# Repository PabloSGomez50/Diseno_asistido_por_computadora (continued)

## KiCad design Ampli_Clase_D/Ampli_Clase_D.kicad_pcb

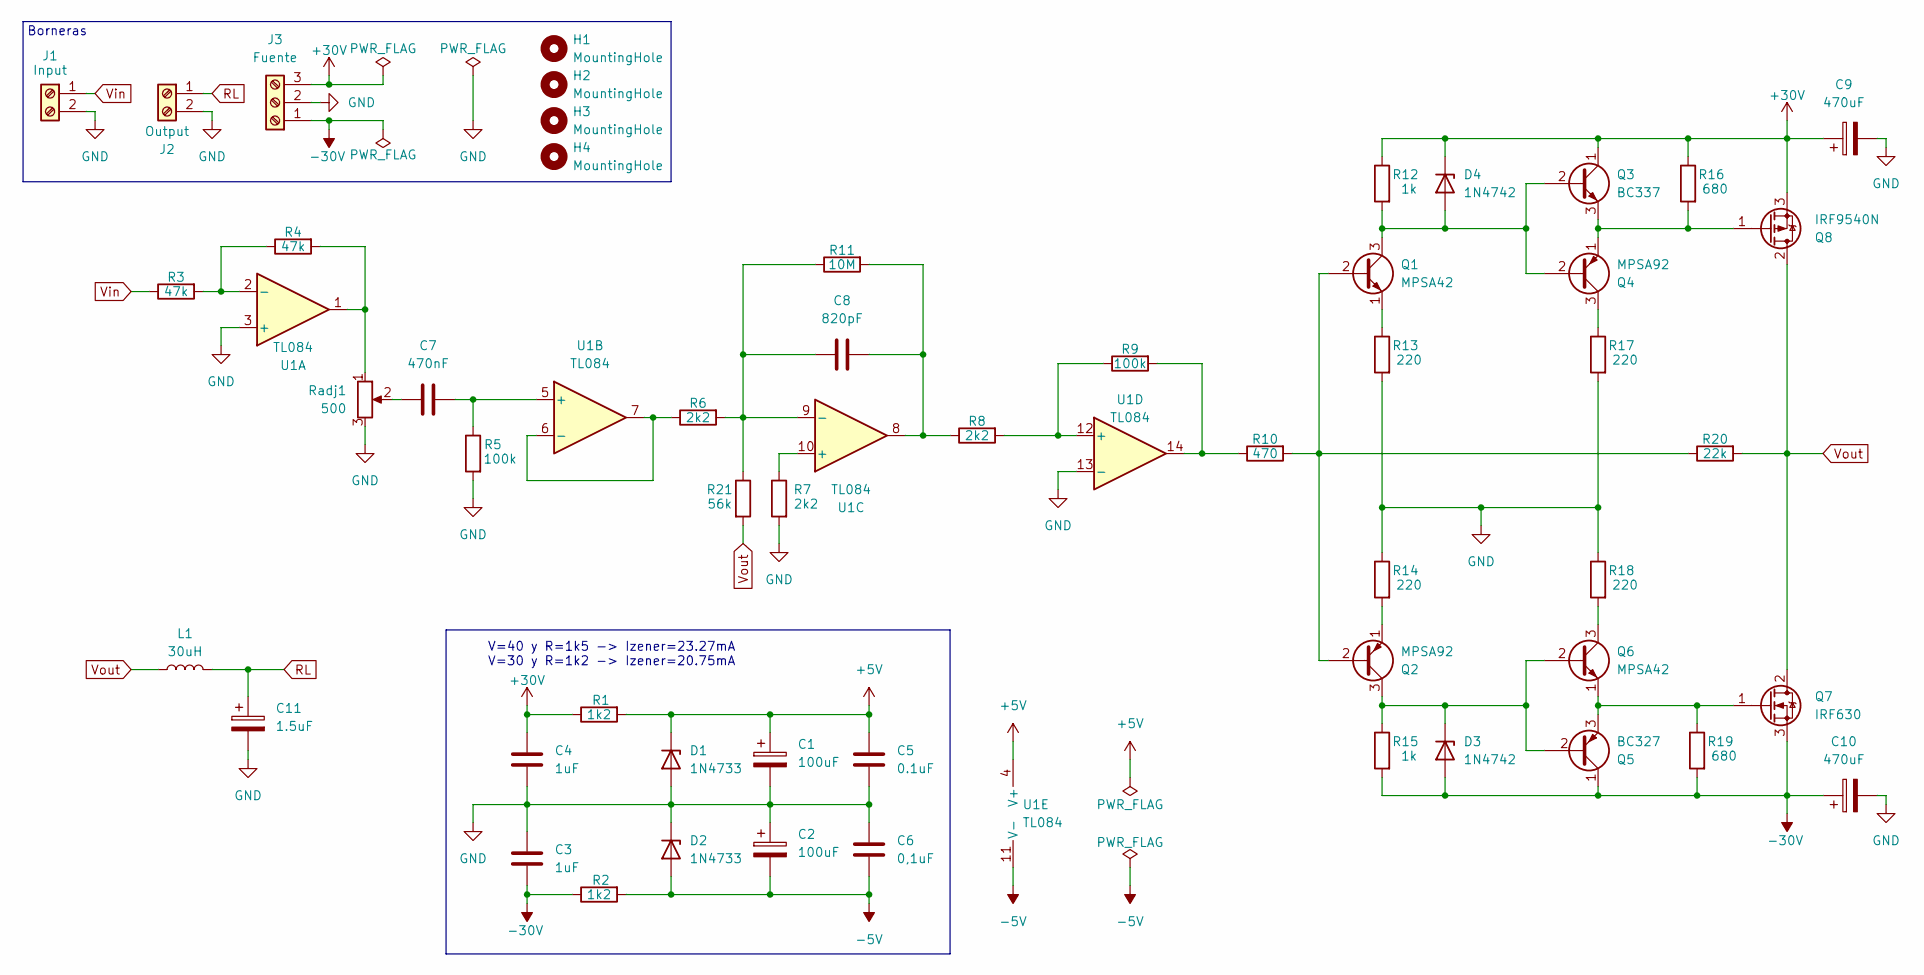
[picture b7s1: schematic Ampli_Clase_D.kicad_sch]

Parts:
C1, C2: 100uF; CP_Radial_D5.0mm_P2.50mm
C3, C4: 1uF; C_Disc_D3.0mm_W2.0mm_P2.50mm
C5: 0.1uF; C_Disc_D3.0mm_W2.0mm_P2.50mm
C6: 0,1uF; C_Disc_D3.0mm_W2.0mm_P2.50mm
C7: 470nF; C_Disc_D3.0mm_W2.0mm_P2.50mm
C8: 820pF; C_Disc_D3.0mm_W2.0mm_P2.50mm
C9, C10: 470uF; CP_Radial_D5.0mm_P2.50mm
C11: 1.5uF; CP_Radial_D5.0mm_P2.50mm
D1, D2: 1N4733; D_A-405_P10.16mm_Horizontal
D3, D4: 1N4742; D_A-405_P10.16mm_Horizontal
H1, H2, H3, H4: MountingHole; MountingHole_3.2mm_M3
J1: Input; TerminalBlock_Phoenix_MKDS-1,5-2-5.08_1x02_P5.08mm_Horizont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
J2: Output; TerminalBlock_Phoenix_MKDS-1,5-2-5.08_1x02_P5.08mm_Horizont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
J3: Fuente; TerminalBlock_Phoenix_MKDS-1,5-3-5.08_1x03_P5.08mm_Horizont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
L1: 30uH; Choke_Schaffner_RN204-04-9.0x14.0mm
Q1, Q6: MPSA42; TO-92_Inline
Q2, Q4: MPSA92; TO-92_Inline
Q3: BC337; TO-92_Inline
Q5: BC327; TO-92_Inline
Q7: IRF630; TO-220-3_Vertical
Q8: IRF9540N; TO-220-3_Vertical
R1, R2: 1k2; R_Axial_DIN0207_L6.3mm_D2.5mm_P10.16mm_Horizontal
R3, R4: 47k; R_Axial_DIN0207_L6.3mm_D2.5mm_P10.16mm_Horizontal
R5, R9: 100k; R_Axial_DIN0207_L6.3mm_D2.5mm_P10.16mm_Horizontal
R6, R7, R8: 2k2; R_Axial_DIN0207_L6.3mm_D2.5mm_P10.16mm_Horizontal
R10: 470; R_Axial_DIN0207_L6.3mm_D2.5mm_P10.16mm_Horizontal
R11: 10M; R_Axial_DIN0207_L6.3mm_D2.5mm_P10.16mm_Horizontal
R12, R15: 1k; R_Axial_DIN0207_L6.3mm_D2.5mm_P10.16mm_Horizontal
R13, R14, R17, R18: 220; R_Axial_DIN0207_L6.3mm_D2.5mm_P10.16mm_Horizontal
R16, R19: 680; R_Axial_DIN0207_L6.3mm_D2.5mm_P10.16mm_Horizontal
R20: 22k; R_Axial_DIN0207_L6.3mm_D2.5mm_P10.16mm_Horizontal
R21: 56k; R_Axial_DIN0207_L6.3mm_D2.5mm_P10.16mm_Horizontal
Radj1: 500; PinHeader_1x03_P2.54mm_Vertical
U1: TL084; DIP-14_W7.62mm

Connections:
+5V: C1.1, C5.1, D1.1 (K), R1.2, U1.4 (V+)
+30V: C4.1, C9.1, D4.1 (K), J3.3, Q3.1 (C), Q8.3 (S), R1.1, R12.1, R16.1
-5V: C2.2, C6.2, D2.2 (A), R2.2, U1.11 (V-)
-30V: C3.2, C10.1, D3.2 (A), J3.1, Q5.1 (C), Q7.3 (S), R2.1, R15.2, R19.2
GND: C1.2, C2.1, C3.1, C4.2, C5.2, C6.1, C9.2, C10.2, C11.2, D1.2 (A), D2.1 (K), J1.2, J2.2, J3.2, R5.2, R7.2, R13.2, R14.1, R17.2, R18.1, Radj1.3, U1.3 (+), U1.13 (-)
unnamed: C7.1, Radj1.2
unnamed: C8.2, R8.1, R11.2, U1.8
unnamed: D3.1 (K), Q2.3 (C), Q5.2 (B), Q6.2 (B), R15.1
unnamed: D4.2 (A), Q1.3 (C), Q3.2 (B), Q4.2 (B), R12.2
unnamed: Q1.2 (B), Q2.2 (B), R10.2, R20.1
unnamed: Q1.1 (E), R13.1
unnamed: Q2.1 (E), R14.2
unnamed: Q3.3 (E), Q4.1 (E), Q8.1 (G), R16.2
unnamed: Q4.3 (C), R17.1
unnamed: Q5.3 (E), Q6.1 (E), Q7.1 (G), R19.1
unnamed: Q6.3 (C), R18.2
unnamed: R4.2, Radj1.1, U1.1
unnamed: R9.2, R10.1, U1.14
unnamed: R3.2, R4.1, U1.2 (-)
unnamed: C7.2, R5.1, U1.5 (+)
unnamed: R6.1, U1.6 (-), U1.7
unnamed: R7.1, U1.10 (+)
unnamed: C8.1, R6.2, R11.1, R21.1, U1.9 (-)
unnamed: R8.2, R9.1, U1.12 (+)
RL: C11.1, J2.1, L1.2
Vin: J1.1, R3.1
Vout: L1.1, Q7.2 (D), Q8.2 (D), R20.2, R21.2

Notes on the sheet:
Borneras
V=40 y R=1k5 -> Izener=23.27mA V=30 y R=1k2 -> Izener=20.75mA

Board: 2 copper layers, 54 parts (0 on the bottom side), 27 nets, no tracks yet.

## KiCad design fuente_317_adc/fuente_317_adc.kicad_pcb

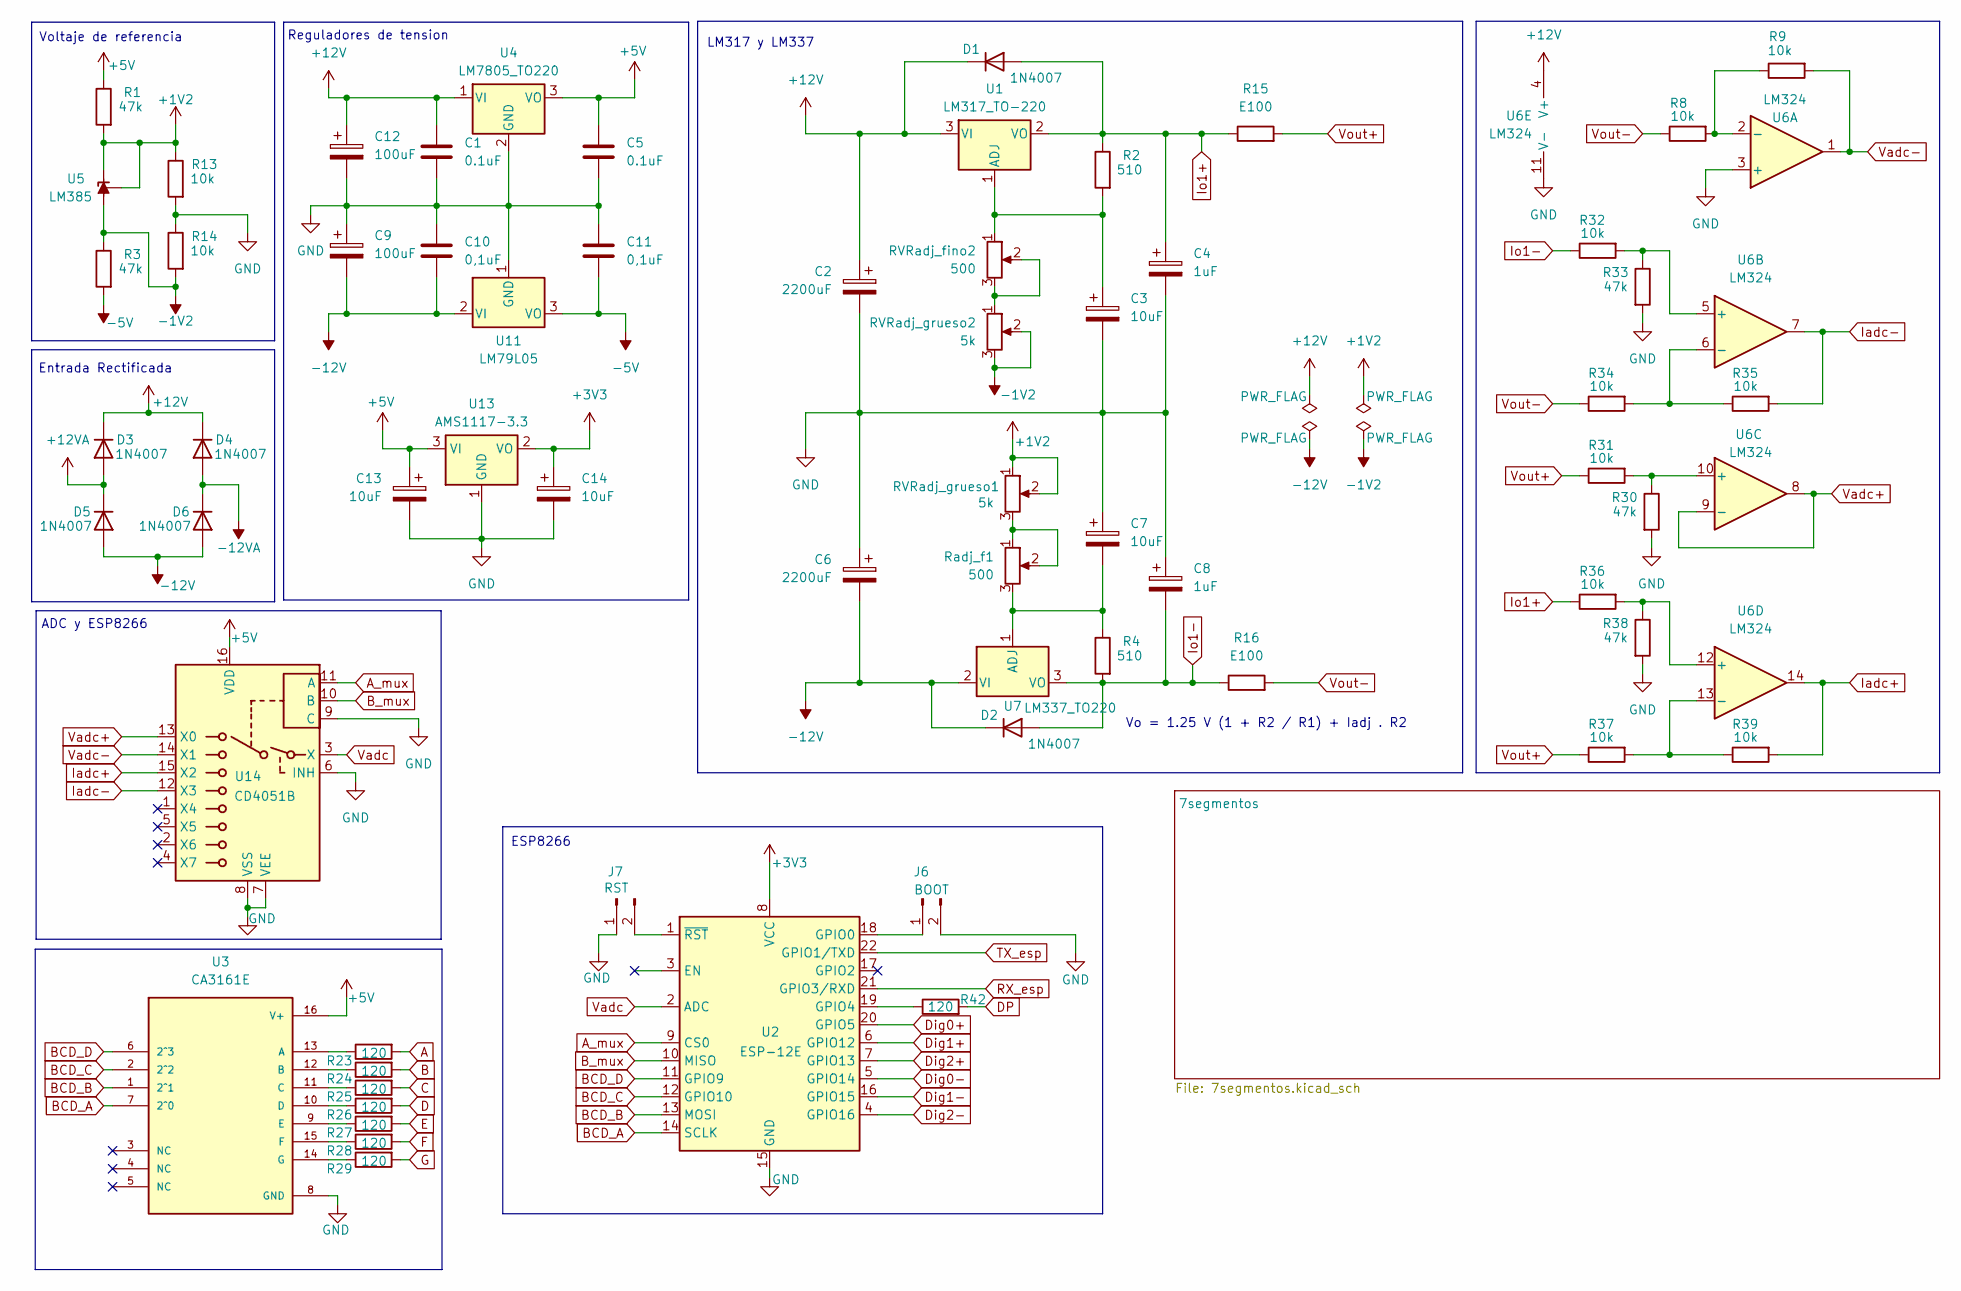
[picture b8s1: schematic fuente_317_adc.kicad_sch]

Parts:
C1, C5: 0.1uF; C_Disc_D3.0mm_W2.0mm_P2.50mm
C2, C6: 2200uF; CP_Radial_D16.0mm_P7.50mm
C3, C7, C13, C14: 10uF; CP_Radial_D5.0mm_P2.50mm
C4, C8: 1uF; CP_Radial_D5.0mm_P2.50mm
C9, C12: 100uF; CP_Radial_D5.0mm_P2.50mm
C10, C11: 0,1uF; C_Disc_D3.0mm_W2.0mm_P2.50mm
D1, D2, D3, D4, D5, D6: 1N4007; D_DO-41_SOD81_P10.16mm_Horizontal
J6: BOOT; PinHeader_1x02_P2.54mm_Vertical
J7: RST; PinHeader_1x02_P2.54mm_Vertical
R1, R3, R30, R33, R38: 47k; R_Axial_DIN0207_L6.3mm_D2.5mm_P10.16mm_Horizontal
R2, R4: 510; R_Axial_DIN0207_L6.3mm_D2.5mm_P10.16mm_Horizontal
R8, R9, R13, R14, R31, R32, R34, R35, R36, R37, R39: 10k; R_Axial_DIN0207_L6.3mm_D2.5mm_P10.16mm_Horizontal
R15, R16: E100; R_Axial_Power_L25.0mm_W6.4mm_P30.48mm
R23, R24, R25, R26, R27, R28, R29, R42: 120; R_Axial_DIN0207_L6.3mm_D2.5mm_P10.16mm_Horizontal
RVRadj_fino2: 500; PinHeader_1x03_P2.54mm_Vertical
RVRadj_grueso1, RVRadj_grueso2: 5k; PinHeader_1x03_P2.54mm_Vertical
Radj_f1: 500; PinHeader_1x03_P2.54mm_Vertical
U1: LM317_TO-220; TO-220-3_Vertical
U2: ESP-12E
U3: CA3161E; DIP793W45P254L1917H533Q16; PARTREV 3.00
U4: LM7805_TO220; TO-220-3_Vertical
U5: LM385; TO-92_Inline
U6: LM324; CERDIP-14_W7.62mm_SideBrazed_Socket
U7: LM337_TO220; TO-220-3_Vertical
U11: LM79L05; TO-92_Inline
U13: AMS1117-3.3; SOT-223-3_TabPin2
U14: CD4051B; CERDIP-16_W7.62mm_SideBrazed_Socket

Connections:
+1V2: R1.2, R13.1, RVRadj_grueso1.1, RVRadj_grueso1.2, U5.1 (REF), U5.3 (K)
+3V3: C14.1, U2.8 (VCC), U13.2 (VO)
+5V: C5.1, C13.1, R1.1, U3.16 (V+), U4.3 (VO), U13.3 (VI), U14.16 (VDD); also elsewhere on the board
+12V: C1.1, C2.1, C12.1, D1.1 (K), D3.1 (K), D4.1 (K), U1.3 (VI), U4.1 (VI), U6.4 (V+)
+12VA: D3.2 (A), D5.1 (K); also elsewhere on the board
-1V2: R3.1, R14.2, RVRadj_grueso2.2, RVRadj_grueso2.3, U5.2 (A)
-5V: C11.2, R3.2, U11.3 (VO)
-12V: C6.2, C9.2, C10.2, D2.1 (K), D5.2 (A), D6.2 (A), U7.2 (VI), U11.2 (VI)
-12VA: D4.2 (A), D6.1 (K); also elsewhere on the board
A: R23.2; also elsewhere on the board
A_mux: U2.9 (CS0), U14.11 (A)
B: R24.2; also elsewhere on the board
BCD_A: U2.14 (SCLK), U3.7 (2^0)
BCD_B: U2.13 (MOSI), U3.1 (2^1)
BCD_C: U2.12 (GPIO10), U3.2 (2^2)
BCD_D: U2.11 (GPIO9), U3.6 (2^3)
B_mux: U2.10 (MISO), U14.10 (B)
C: R25.2; also elsewhere on the board
D: R26.2; also elsewhere on the board
DP: R42.2; also elsewhere on the board
Dig0+: U2.20 (GPIO5); also elsewhere on the board
Dig0-: U2.5 (GPIO14); also elsewhere on the board
Dig1+: U2.6 (GPIO12); also elsewhere on the board
Dig1-: U2.16 (GPIO15); also elsewhere on the board
Dig2+: U2.7 (GPIO13); also elsewhere on the board
Dig2-: U2.4 (GPIO16); also elsewhere on the board
E: R27.2; also elsewhere on the board
F: R28.2; also elsewhere on the board
G: R29.2; also elsewhere on the board
GND: C1.2, C2.2, C3.2, C4.2, C5.2, C6.1, C7.1, C8.1, C9.1, C10.1, C11.1, C12.2, C13.2, C14.2, J6.2, J7.1, R13.2, R14.1, R30.2, R33.2, R38.2, U2.15 (GND), U3.8 (GND), U4.2 (GND), U6.3 (+), U6.11 (V-), U11.1 (GND), U13.1 (GND), U14.6 (INH), U14.7 (VEE), U14.8 (VSS), U14.9 (C); also elsewhere on the board
Iadc+: R39.2, U6.14, U14.15 (X2)
Iadc-: R35.2, U6.7, U14.12 (X3)
Io1+: C4.1, D1.2 (A), R2.1, R15.1, R36.1, U1.2 (VO)
Io1-: C8.2, D2.2 (A), R4.2, R16.1, R32.1, U7.3 (VO)
unnamed: J6.1, U2.18 (GPIO0)
unnamed: J7.2, U2.1 (~RST)
unnamed: RVRadj_fino2.2, RVRadj_fino2.3, RVRadj_grueso2.1
unnamed: RVRadj_grueso1.3, Radj_f1.1, Radj_f1.2
unnamed: C3.1, R2.2, RVRadj_fino2.1, U1.1 (ADJ)
unnamed: R42.1, U2.19 (GPIO4)
unnamed: R23.1, U3.13 (A)
unnamed: R24.1, U3.12 (B)
unnamed: R25.1, U3.11 (C)
unnamed: R26.1, U3.10 (D)
unnamed: R27.1, U3.9 (E)
unnamed: R28.1, U3.15 (F)
unnamed: R29.1, U3.14 (G)
unnamed: R8.2, R9.1, U6.2 (-)
unnamed: R32.2, R33.1, U6.5 (+)
unnamed: R34.2, R35.1, U6.6 (-)
unnamed: R30.1, R31.2, U6.10 (+)
unnamed: R36.2, R38.1, U6.12 (+)
unnamed: R37.2, R39.1, U6.13 (-)
unnamed: C7.2, R4.1, Radj_f1.3, U7.1 (ADJ)
RX_esp: U2.21 (GPIO3/RXD); also elsewhere on the board
TX_esp: U2.22 (GPIO1/TXD); also elsewhere on the board
Vadc: U2.2 (ADC), U14.3 (X)
Vadc+: U6.8, U6.9 (-), U14.13 (X0)
Vadc-: R9.2, U6.1, U14.14 (X1)
Vout+: R15.2, R31.1, R37.1; also elsewhere on the board
Vout-: R8.1, R16.2, R34.1; also elsewhere on the board

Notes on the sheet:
Reguladores de tension
Voltaje de referencia
LM317 y LM337
ESP8266
Entrada Rectificada
Vo = 1.25 V (1 + R2 / R1) + Iadj . R2
ADC y ESP8266

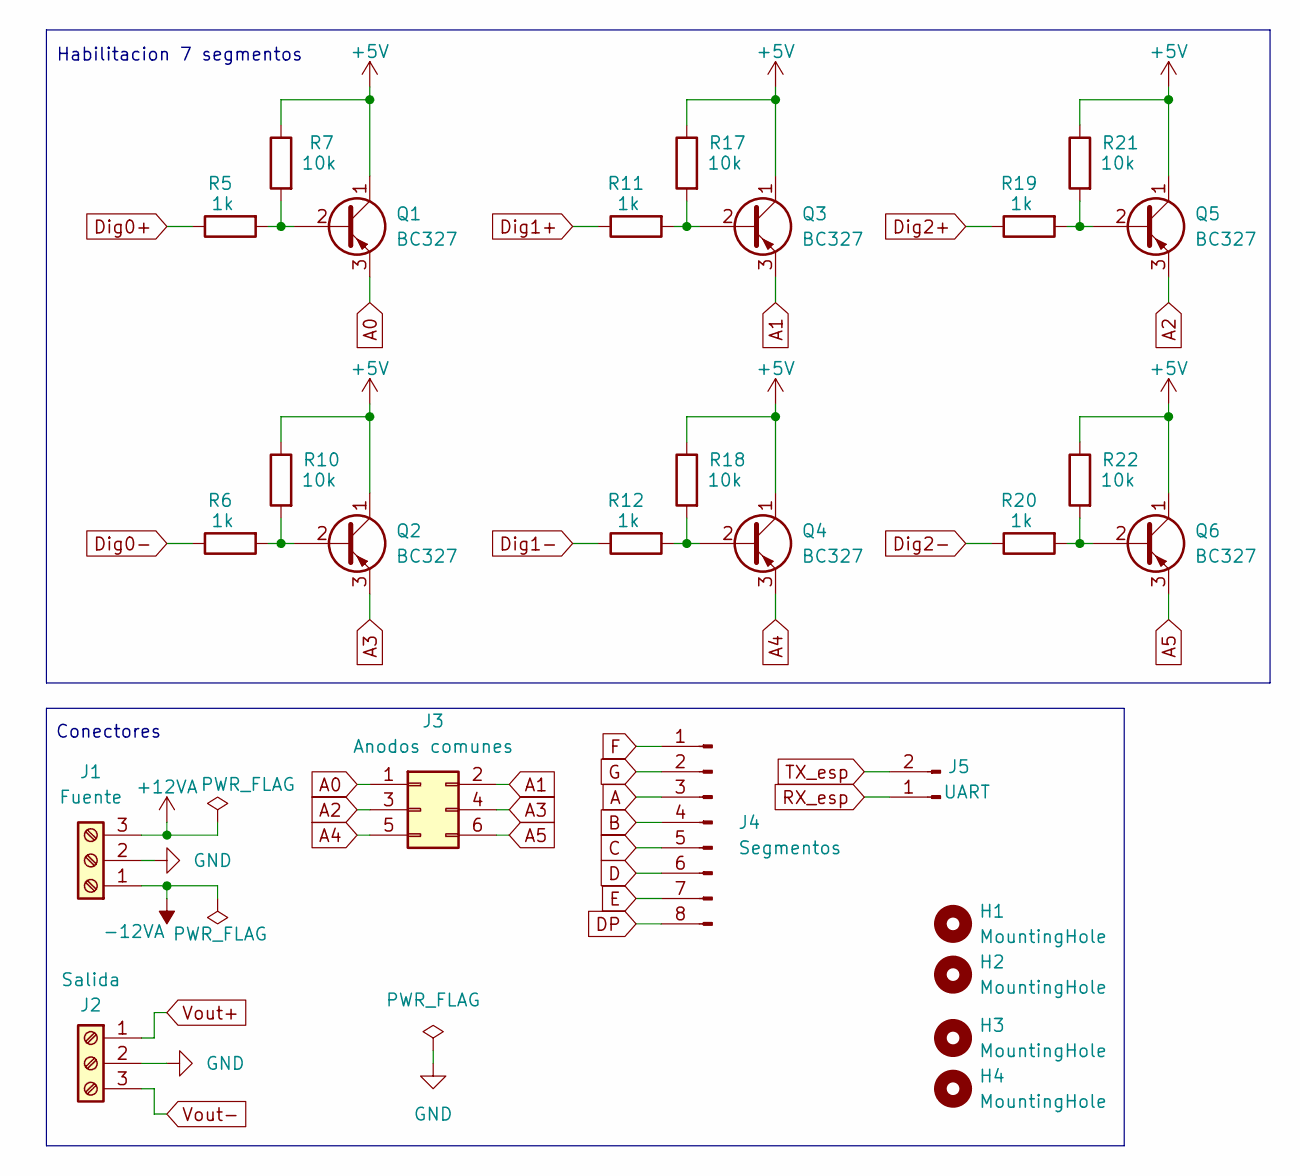
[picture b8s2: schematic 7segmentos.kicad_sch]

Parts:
H1, H2, H3, H4: MountingHole; MountingHole_3.2mm_M3
J1: Fuente; TerminalBlock_Phoenix_MKDS-1,5-3-5.08_1x03_P5.08mm_Horizont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
J2: Salida; TerminalBlock_Phoenix_MKDS-1,5-3-5.08_1x03_P5.08mm_Horizont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
J3: Anodos comunes; PinHeader_2x03_P2.54mm_Vertical
J4: Segmentos; PinHeader_1x08_P2.54mm_Vertical
J5: UART; PinHeader_1x02_P2.54mm_Vertical
Q1, Q2, Q3, Q4, Q5, Q6: BC327; TO-92_Inline
R5, R6, R11, R12, R19, R20: 1k; R_Axial_DIN0207_L6.3mm_D2.5mm_P10.16mm_Horizontal
R7, R10, R17, R18, R21, R22: 10k; R_Axial_DIN0207_L6.3mm_D2.5mm_P10.16mm_Horizontal

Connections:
+5V: Q1.1 (C), Q2.1 (C), Q3.1 (C), Q4.1 (C), Q5.1 (C), Q6.1 (C), R7.1, R10.1, R17.1, R18.1, R21.1, R22.1; also elsewhere on the board
+12VA: J1.3; also elsewhere on the board
-12VA: J1.1; also elsewhere on the board
A: J4.3; also elsewhere on the board
A0: J3.1, Q1.3 (E)
A1: J3.2, Q3.3 (E)
A2: J3.3, Q5.3 (E)
A3: J3.4, Q2.3 (E)
A4: J3.5, Q4.3 (E)
A5: J3.6, Q6.3 (E)
B: J4.4; also elsewhere on the board
C: J4.5; also elsewhere on the board
D: J4.6; also elsewhere on the board
DP: J4.8; also elsewhere on the board
Dig0+: R5.1; also elsewhere on the board
Dig0-: R6.1; also elsewhere on the board
Dig1+: R11.1; also elsewhere on the board
Dig1-: R12.1; also elsewhere on the board
Dig2+: R19.1; also elsewhere on the board
Dig2-: R20.1; also elsewhere on the board
E: J4.7; also elsewhere on the board
F: J4.1; also elsewhere on the board
G: J4.2; also elsewhere on the board
GND: J1.2, J2.2; also elsewhere on the board
unnamed: Q1.2 (B), R5.2, R7.2
unnamed: Q2.2 (B), R6.2, R10.2
unnamed: Q3.2 (B), R11.2, R17.2
unnamed: Q4.2 (B), R12.2, R18.2
unnamed: Q5.2 (B), R19.2, R21.2
unnamed: Q6.2 (B), R20.2, R22.2
RX_esp: J5.1; also elsewhere on the board
TX_esp: J5.2; also elsewhere on the board
Vout+: J2.1; also elsewhere on the board
Vout-: J2.3; also elsewhere on the board

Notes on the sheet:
Habilitacion 7 segmentos
Conectores

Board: 2 copper layers, 91 parts (2 on the bottom side), 73 nets, no tracks yet.

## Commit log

2024-10-25 init repo
2024-10-25 fuente_317_337: start to wire OP AMP
2024-10-26 Add LPC files
2024-10-26 Change position of LM7805 and 3v3
2024-10-28 fuente_317_337: pcb finalizado de fuente y controlador
2024-10-28 fix ground plane in fuente_317_337
2024-10-31 Complete ej 2 of tp9
2024-11-02 pcb minimal change
2024-11-02 fix: protection diode
2024-11-03 finish tp8
2024-11-03 Finish tp10
2024-11-04 feat: version final para el tp integrador
